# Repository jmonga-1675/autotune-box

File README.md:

# autotune-box
Karaoke autotuner for HOPE final project

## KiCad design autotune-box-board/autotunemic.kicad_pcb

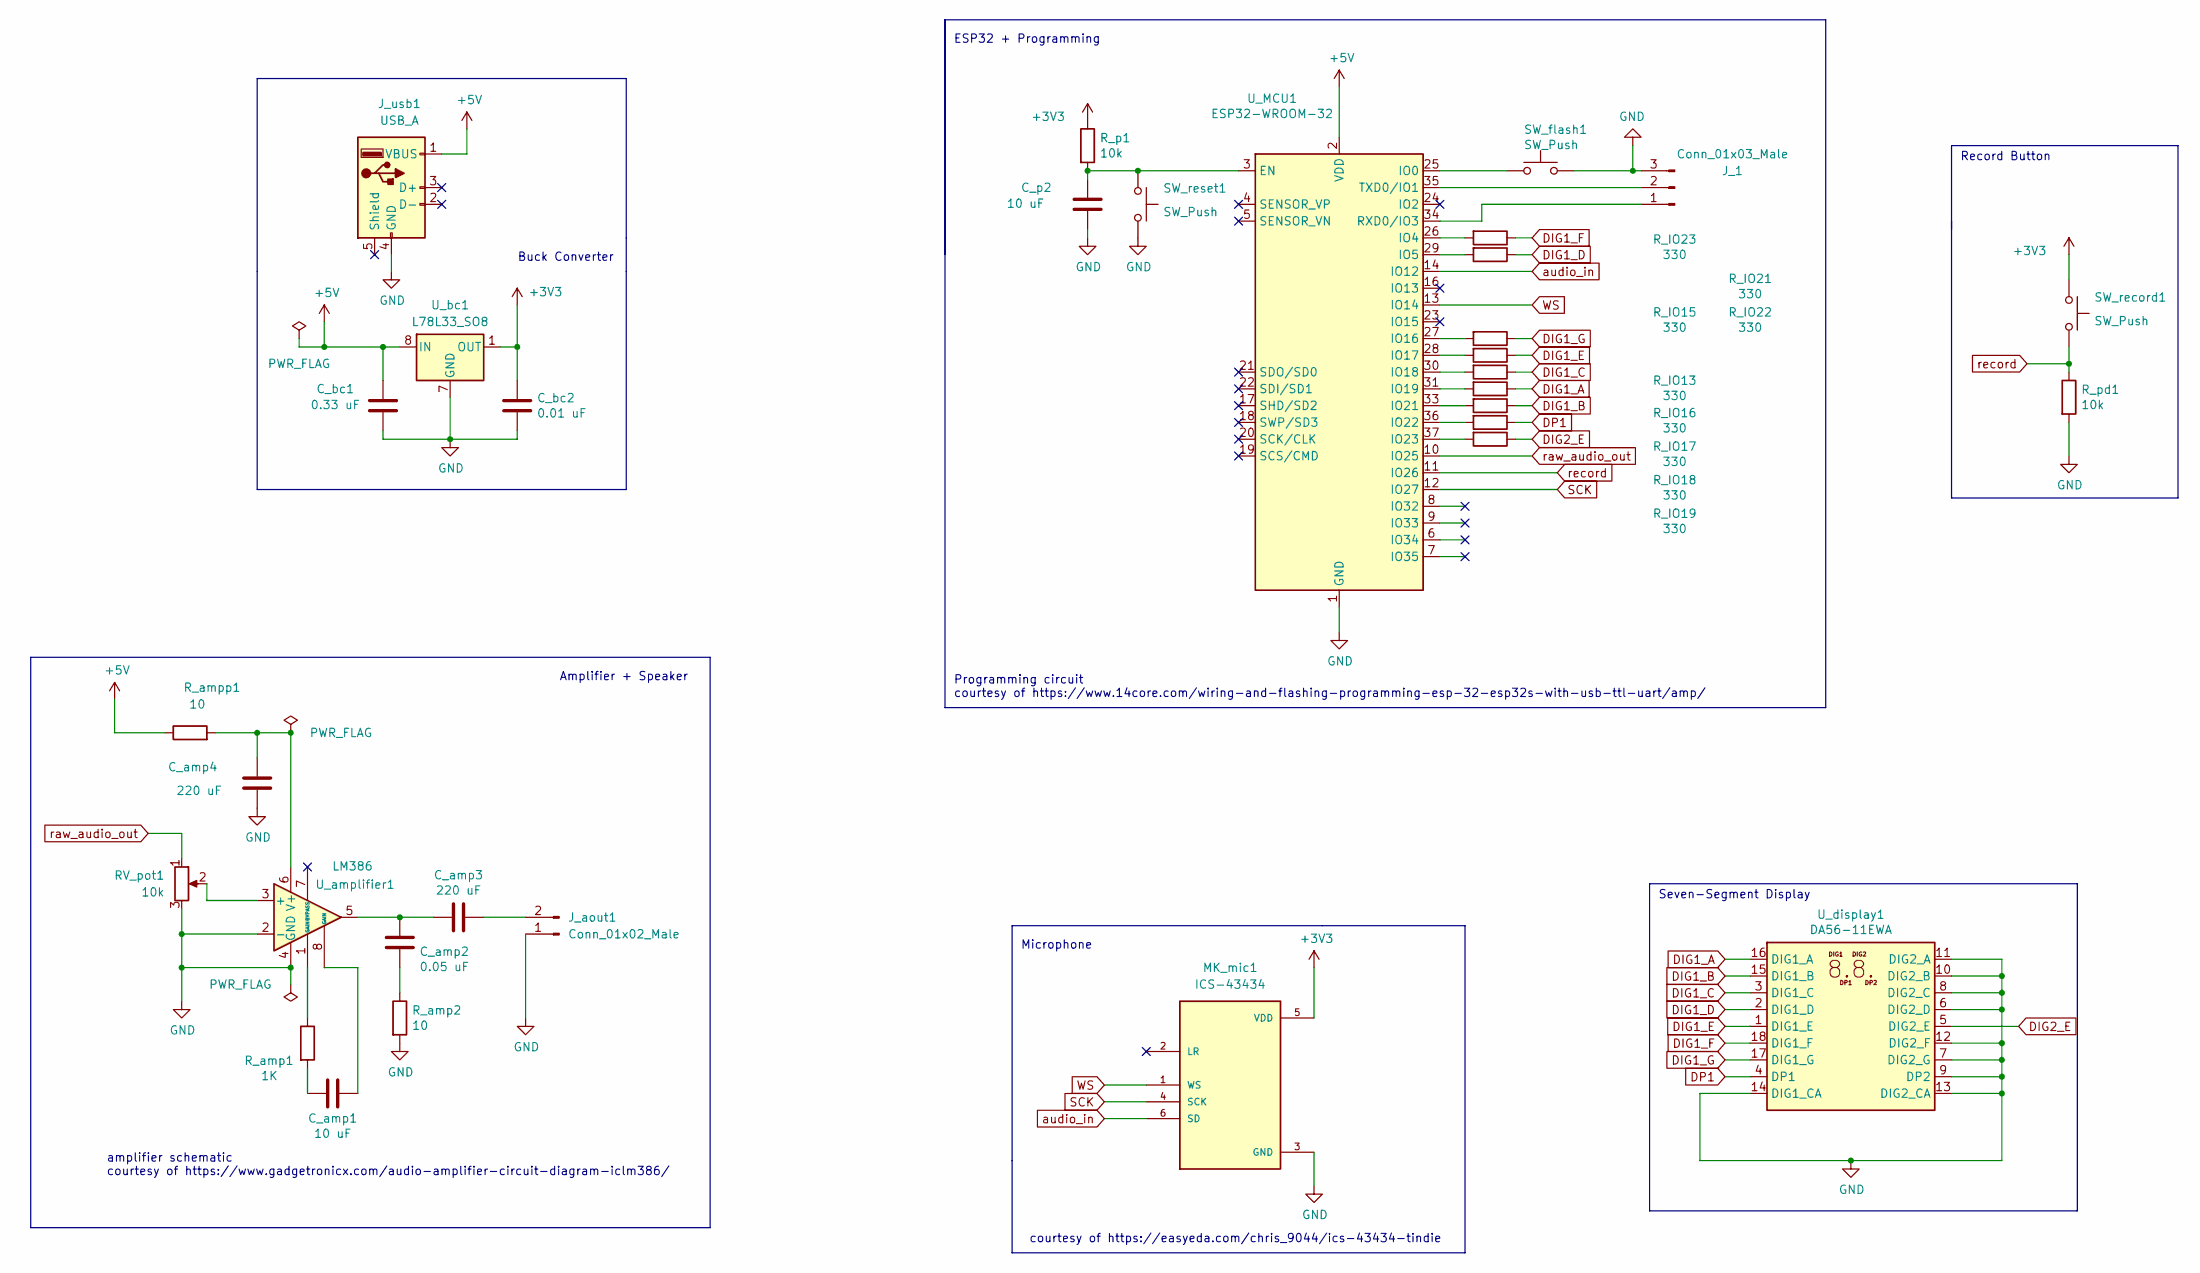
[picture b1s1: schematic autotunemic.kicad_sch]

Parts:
C_amp1: 10 uF; C_1206_3216Metric
C_amp2: 0.05 uF; C_1206_3216Metric
C_amp3, C_amp4: 220 uF; C_1206_3216Metric
C_bc1: 0.33 uF; C_1206_3216Metric
C_bc2: 0.01 uF; C_1206_3216Metric
C_p2: 10 uF; C_1206_3216Metric
J_1: Conn_01x03_Male; PinHeader_1x03_P2.54mm_Vertical
J_aout1: Conn_01x02_Male; PinHeader_1x02_P2.54mm_Vertical
J_usb1: USB_A; USB_A_Stewart_SS-52100-001_Horizontal
MK_mic1: ICS-43434; MIC_ICS-43434
RV_pot1: 10k; Potentiometer_Bourns_3214W_Vertical
R_IO13, R_IO15, R_IO16, R_IO17, R_IO18, R_IO19, R_IO21, R_IO22, R_IO23: 330; R_0603_1608Metric
R_amp1: 1K; R_0603_1608Metric
R_amp2: 10; R_0603_1608Metric
R_ampp1: 10; R_0603_1608Metric
R_p1: 10k; R_0603_1608Metric
R_pd1: 10k; R_0603_1608Metric
SW_flash1: SW_Push; SW_SPST_PTS645
SW_record1: SW_Push; SW_SPST_PTS645
SW_reset1: SW_Push; SW_SPST_PTS645
U_MCU1: ESP32-WROOM-32
U_amplifier1: LM386; SOP65P490X110-8N
U_bc1: L78L33_SO8; SOIC-8_3.9x4.9mm_P1.27mm
U_display1: DA56-11EWA; DA56-11SURKWA

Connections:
+3V3: C_bc2.1, MK_mic1.5 (VDD), R_p1.1, SW_record1.1, U_bc1.1 (OUT)
+5V: C_bc1.1, J_usb1.1 (VBUS), R_ampp1.1, U_MCU1.2 (VDD), U_bc1.8 (IN)
DIG1_A: R_IO19.1, U_display1.16 (DIG1_A)
DIG1_B: R_IO21.1, U_display1.15 (DIG1_B)
DIG1_C: R_IO18.1, U_display1.3 (DIG1_C)
DIG1_D: R_IO15.1, U_display1.2 (DIG1_D)
DIG1_E: R_IO17.1, U_display1.1 (DIG1_E)
DIG1_F: R_IO23.1, U_display1.18 (DIG1_F)
DIG1_G: R_IO16.1, U_display1.17 (DIG1_G)
DIG2_E: R_IO13.1, U_display1.5 (DIG2_E)
DP1: R_IO22.1, U_display1.4 (DP1)
GND: C_amp4.2, C_bc1.2, C_bc2.2, C_p2.2, J_1.3, J_aout1.1, J_usb1.4 (GND), MK_mic1.3 (GND), RV_pot1.3, R_amp2.2, R_pd1.2, SW_flash1.2, SW_reset1.2, U_MCU1.1 (GND), U_MCU1.15 (GND), U_MCU1.38 (GND), U_MCU1.39 (GND), U_amplifier1.2 (-), U_amplifier1.4 (GND), U_bc1.2 (GND), U_bc1.3 (GND), U_bc1.6 (GND), U_bc1.7 (GND), U_display1.6 (DIG2_D), U_display1.7 (DIG2_G), U_display1.8 (DIG2_C), U_display1.9 (DP2), U_display1.10 (DIG2_B), U_display1.11 (DIG2_A), U_display1.12 (DIG2_F), U_display1.13 (DIG2_CA), U_display1.14 (DIG1_CA)
unnamed: C_amp1.1, U_amplifier1.8 (GAIN)
unnamed: C_amp1.2, R_amp1.2
unnamed: C_amp2.1, C_amp3.2, U_amplifier1.5
unnamed: C_amp2.2, R_amp2.1
unnamed: C_amp3.1, J_aout1.2
unnamed: C_amp4.1, R_ampp1.2, U_amplifier1.6 (V+)
unnamed: C_p2.1, R_p1.2, SW_reset1.1, U_MCU1.3 (EN)
unnamed: J_1.1, U_MCU1.34 (RXD0/IO3)
unnamed: J_1.2, U_MCU1.35 (TXD0/IO1)
unnamed: RV_pot1.2, U_amplifier1.3 (+)
unnamed: R_IO13.2, U_MCU1.37 (IO23)
unnamed: R_IO15.2, U_MCU1.29 (IO5)
unnamed: R_IO16.2, U_MCU1.27 (IO16)
unnamed: R_IO17.2, U_MCU1.28 (IO17)
unnamed: R_IO18.2, U_MCU1.30 (IO18)
unnamed: R_IO21.2, U_MCU1.33 (IO21)
unnamed: R_IO22.2, U_MCU1.36 (IO22)
unnamed: R_IO23.2, U_MCU1.26 (IO4)
unnamed: R_amp1.1, U_amplifier1.1 (GAIN)
unnamed: SW_flash1.1, U_MCU1.25 (IO0)
unnamed: R_IO19.2, U_MCU1.31 (IO19)
SCK: MK_mic1.4 (SCK), U_MCU1.12 (IO27)
WS: MK_mic1.1 (WS), U_MCU1.13 (IO14)
audio_in: MK_mic1.6 (SD), U_MCU1.14 (IO12)
raw_audio_out: RV_pot1.1, U_MCU1.10 (IO25)
record: R_pd1.1, SW_record1.2, U_MCU1.11 (IO26)

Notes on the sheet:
Amplifier + Speaker
Programming circuit courtesy of https://www.14core.com/wiring-and-flashing-programming-esp-32-esp32s-with-usb-ttl-uart/amp/
Seven-Segment Display
Record Button
ESP32 + Programming
amplifier schematic courtesy of https://www.gadgetronicx.com/audio-amplifier-circuit-diagram-iclm386/
Microphone
Buck Converter
courtesy of https://easyeda.com/chris_9044/ics-43434-tindie

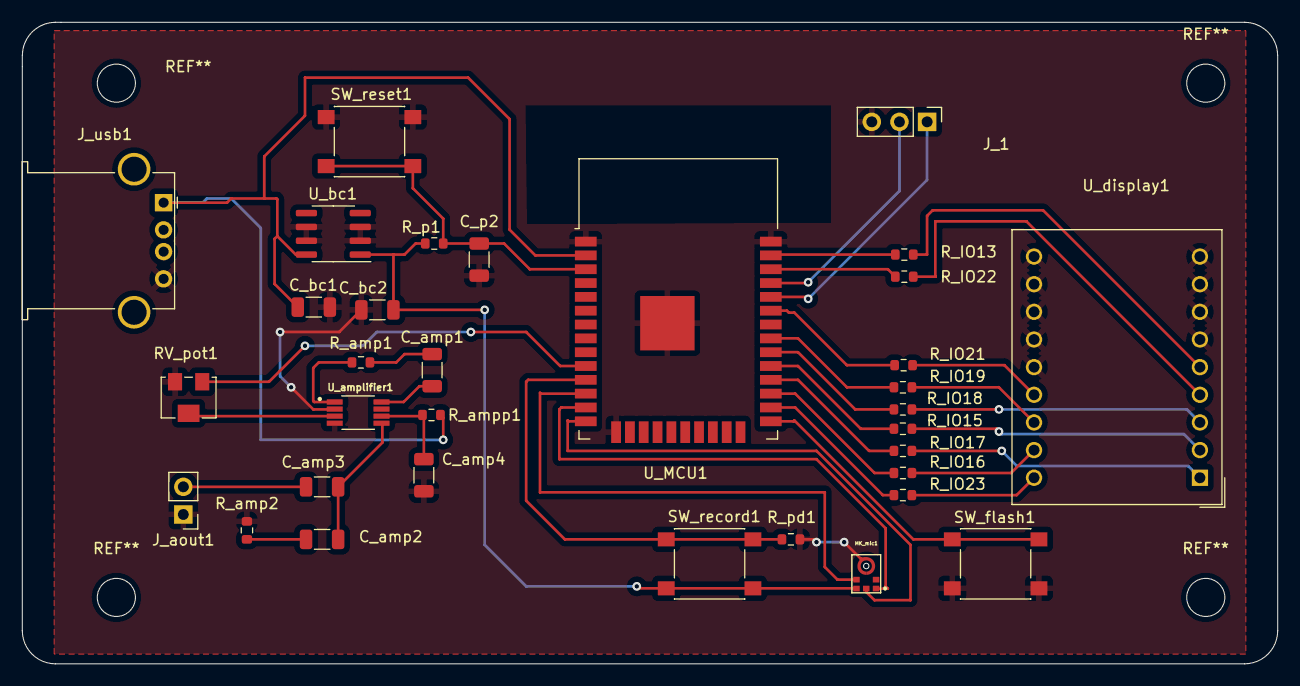
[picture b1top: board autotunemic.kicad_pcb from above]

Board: 2 copper layers, 115.3 x 58.9 mm, 33 parts (0 on the bottom side), 38 nets.

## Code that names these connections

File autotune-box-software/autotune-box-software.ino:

#include "driver/i2s.h"
#include "arduinoFFT.h"

// Pin definitions
// Display
const uint8_t DIG1_A = GPIO_NUM_19;
const uint8_t DIG1_B = GPIO_NUM_21;
const uint8_t DIG1_C = GPIO_NUM_18;
const uint8_t DIG1_D = GPIO_NUM_5;
const uint8_t DIG1_E = GPIO_NUM_17;
const uint8_t DIG1_F = GPIO_NUM_4;
const uint8_t DIG2_B = GPIO_NUM_21;
const uint8_t DP1 = GPIO_NUM_22;

// Record button
const uint8_t RECORD = GPIO_NUM_26;

// MIC
const uint8_t AUDIO_IN = GPIO_NUM_26;
const uint8_t AUDIO_SCK = GPIO_NUM_27;
const uint8_t AUDIO_WS = GPIO_NUM_14;

// Mic out
const uint8_t AUDIO_OUT = GPIO_NUM_25;

// I2S Port
const i2s_port_t I2S_PORT = I2S_NUM_1;

// FFT Params
const uint16_t SAMPLE_FREQUENCY = 32000;

void setup() {
  Serial.begin(115200);
  esp_err_t err;

  i2s_config_t i2s_config = {
    .mode = (i2s_mode_t)(I2S_MODE_MASTER | I2S_MODE_RX),
    .sample_rate = 20000,
    .bits_per_sample = I2S_BITS_PER_SAMPLE_32BIT,
    .channel_format = I2S_CHANNEL_FMT_ONLY_LEFT,
    .communication_format = i2s_comm_format_t(I2S_COMM_FORMAT_I2S),
    .intr_alloc_flags = ESP_INTR_FLAG_LEVEL1,
    .dma_buf_count = 4,
    .dma_buf_len = 1024,
    .use_apll = false,
    .tx_desc_auto_clear = false,
    .fixed_mclk = 0};

  // The pin config as per the setup
  const i2s_pin_config_t pin_config = {
      .bck_io_num = AUDIO_SCK,   // Serial Clock (SCK)
      .ws_io_num = AUDIO_WS,    // Word Select (WS)
      .data_out_num = I2S_PIN_NO_CHANGE, // not used (only for speakers)
      .data_in_num = AUDIO_IN   // Serial Data (SD)
  };

  // Configuring the I2S driver and pins.
  // This function must be called before any I2S driver read/write operations.
  err = i2s_driver_install(I2S_PORT, &i2s_config, 0, NULL);
  if (err != ESP_OK) {
    Serial.printf("Failed installing driver: %d\n", err);
    while (true);
  }
  err = i2s_set_pin(I2S_PORT, &pin_config);
  if (err != ESP_OK) {
    Serial.printf("Failed setting pin: %d\n", err);
    while (true);
  }
  Serial.println("I2S driver installed.");
}

void loop() {
  // put your main code here, to run repeatedly:
  bool record_state = digitalRead(RECORD);
  if (record_state){
    // Record many data

    // FFT data in set windows

    // Set all data in window to frequency of window

    // Send data to speaker
  }

}

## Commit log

2021-12-08 first commit!
2021-12-08 reee
2021-12-10 yeet
